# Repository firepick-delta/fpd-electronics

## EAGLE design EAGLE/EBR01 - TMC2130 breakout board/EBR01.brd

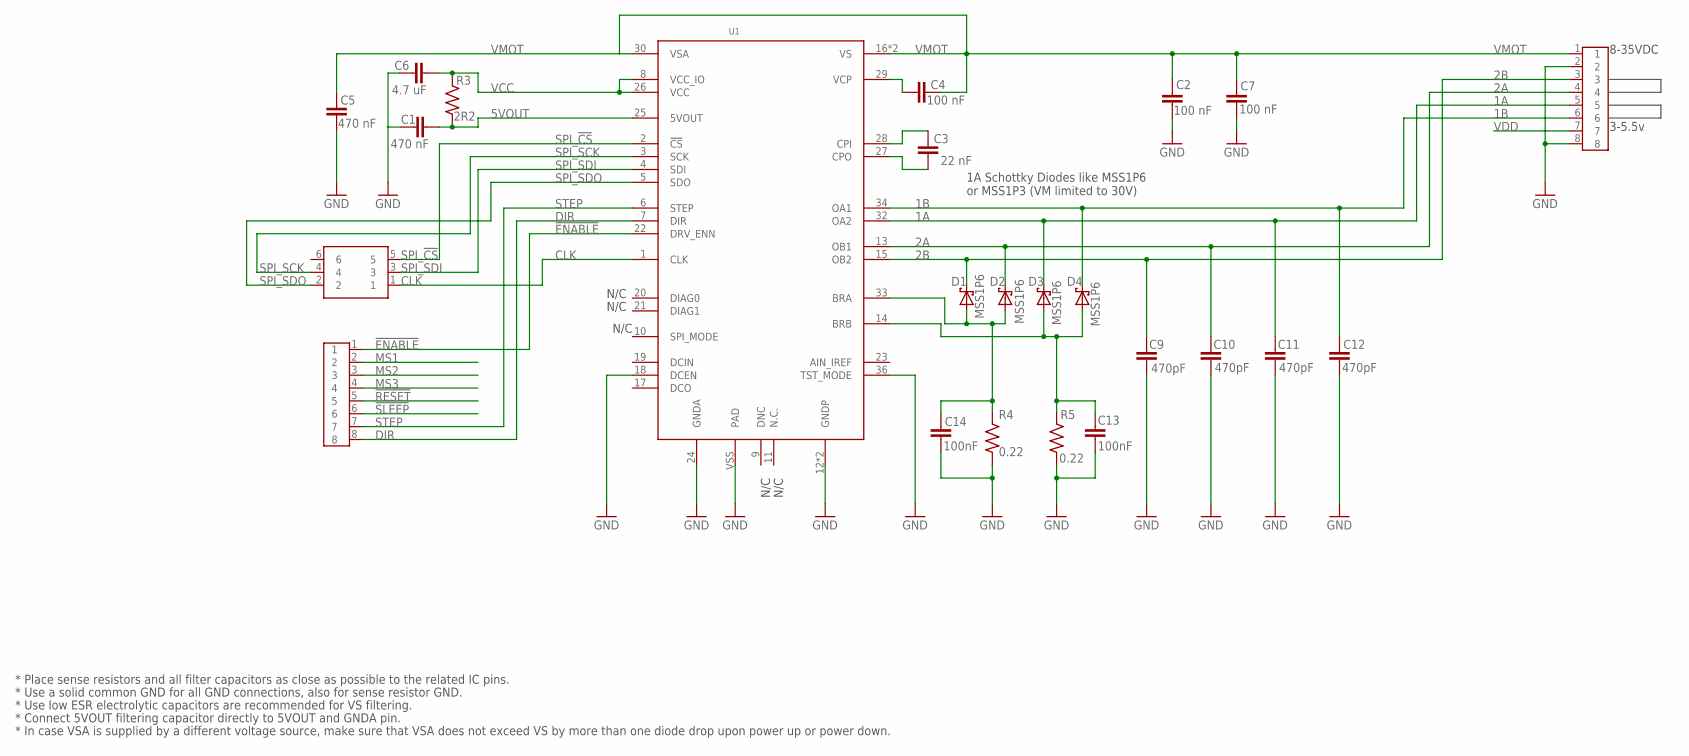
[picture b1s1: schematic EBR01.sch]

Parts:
C1: 470 nF; 0603-CAP
C2, C4, C7: 100 nF; C0603
C3: 22 nF; C0603
C5: 470 nF; C0603
C6: 4.7 uF; C0603
C9, C10, C11, C12: 470pF; C0603
C13, C14: 100nF; C0603
D1, D2, D3, D4: MSS1P6; MICRO-SMP
J1, J2: CPL-CON-HEADER-0.1IN-8P-M; CON-HDR-8POS-MALE
J3: CPL-CON-HEADER-0.1IN-2X3P-M; CON-HDR-2X3P
R3: 2R2; R0603
R4, R5: 0.22; R1206
U1: CPL-MDR-2PHSTEPPER; QFN36-(5X6)

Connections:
1A: C11.1, D3.NEG (C), J2.5, U1.32 (OA2)
1B: C12.1, D4.NEG (C), J2.6, U1.34 (OA1)
2A: C10.1, D2.NEG (C), J2.4, U1.13 (OB1)
2B: C9.1, D1.NEG (C), J2.3, U1.15 (OB2)
5VOUT: C1.1, R3.1, U1.25 (5VOUT)
!ENABLE!: J1.1, U1.22 (DRV_ENN)
!RESET!: J1.5
!SLEEP!: J1.6
CLK: J3.1, U1.1 (CLK)
DIR: J1.8, U1.7 (DIR)
GND: C1.2, C2.2, C5.1, C6.2, C7.2, C9.2, C10.2, C11.2, C12.2, C13.2, C14.2, J2.2, J2.8, R4.1, R5.1, U1.12 (GNDP), U1.18 (DCEN), U1.24 (GNDA), U1.35 (GNDP), U1.36 (TST_MODE), U1.VSS (PAD)
MS1: J1.2
MS2: J1.3
MS3: J1.4
unnamed: C3.2, U1.28 (CPI)
unnamed: C14.1, D1.POS (A), D2.POS (A), R4.2, U1.33 (BRA)
unnamed: C13.1, D3.POS (A), D4.POS (A), R5.2, U1.14 (BRB)
unnamed: C3.1, U1.27 (CPO)
unnamed: C4.1, U1.29 (VCP)
SPI_!CS!: J3.5, U1.2 (!CS)
SPI_SCK: J3.4, U1.3 (SCK)
SPI_SDI: J3.3, U1.4 (SDI)
SPI_SDO: J3.2, U1.5 (SDO)
STEP: J1.7, U1.6 (STEP)
VCC: C6.1, R3.2, U1.8 (VCC_IO), U1.26 (VCC)
VDD: J2.7
VMOT: C2.1, C4.2, C5.2, C7.1, J2.1, U1.16 (VS), U1.30 (VSA), U1.31 (VS)

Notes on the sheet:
3-5.5v
8-35VDC
N/C
* Place sense resistors and all filter capacitors as close as possible to the related IC pins.
* Use a solid common GND for all GND connections, also for sense resistor GND.
* Use low ESR electrolytic capacitors are recommended for VS filtering.
* Connect 5VOUT filtering capacitor directly to 5VOUT and GNDA pin.
* In case VSA is supplied by a different voltage source, make sure that VSA does not exceed VS by more than one diode drop upon power up or power down.
1A Schottky Diodes like MSS1P6 or MSS1P3 (VM limited to 30V)

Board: 2 copper layers, 24 parts (0 on the bottom side), 21 nets, no tracks yet.

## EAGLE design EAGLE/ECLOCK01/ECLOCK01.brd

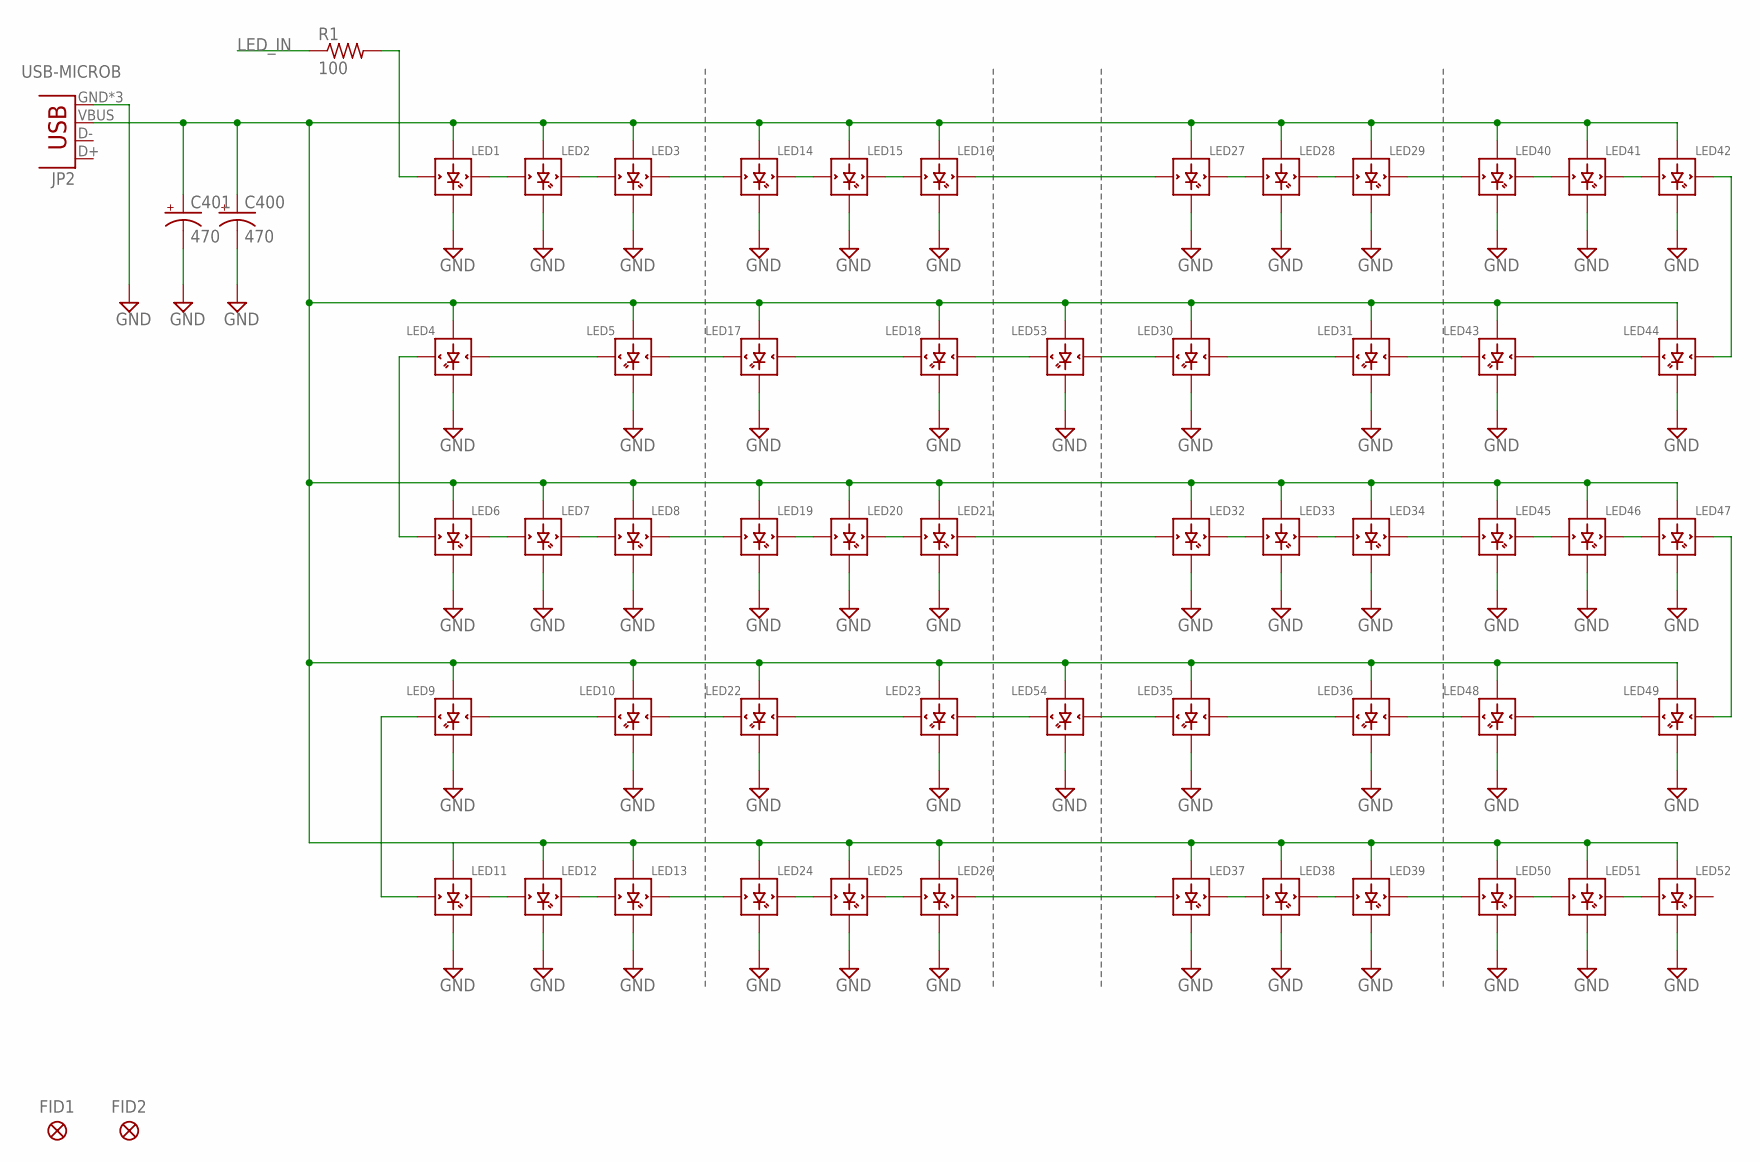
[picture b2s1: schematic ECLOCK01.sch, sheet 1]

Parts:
C400, C401: 470; PANASONIC_E
FID1, FID2: FIDUCIAL
JP2: USB-MICROB
LED1, LED2, LED3, LED4, LED5, LED6, LED7, LED8, LED9, LED10, LED11, LED12, LED13, LED14, LED15, LED16, LED17, LED18, LED19, LED20, LED21, LED22, LED23, LED24, LED25, LED26, LED27, LED28, LED29, LED30, LED31, LED32, LED33, LED34, LED35, LED36, LED37, LED38, LED39, LED40, LED41, LED42, LED43, LED44, LED45, LED46, LED47, LED48, LED49, LED50, LED51, LED52, LED53, LED54: WS2812B
R1: 100; 0805

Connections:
GND: C400.-, C401.-, JP2.GND, JP2.MT1 (GND), JP2.MT2 (GND), LED1.3-GND (GND), LED2.3-GND (GND), LED3.3-GND (GND), LED4.3-GND (GND), LED5.3-GND (GND), LED6.3-GND (GND), LED7.3-GND (GND), LED8.3-GND (GND), LED9.3-GND (GND), LED10.3-GND (GND), LED11.3-GND (GND), LED12.3-GND (GND), LED13.3-GND (GND), LED14.3-GND (GND), LED15.3-GND (GND), LED16.3-GND (GND), LED17.3-GND (GND), LED18.3-GND (GND), LED19.3-GND (GND), LED20.3-GND (GND), LED21.3-GND (GND), LED22.3-GND (GND), LED23.3-GND (GND), LED24.3-GND (GND), LED25.3-GND (GND), LED26.3-GND (GND), LED27.3-GND (GND), LED28.3-GND (GND), LED29.3-GND (GND), LED30.3-GND (GND), LED31.3-GND (GND), LED32.3-GND (GND), LED33.3-GND (GND), LED34.3-GND (GND), LED35.3-GND (GND), LED36.3-GND (GND), LED37.3-GND (GND), LED38.3-GND (GND), LED39.3-GND (GND), LED40.3-GND (GND), LED41.3-GND (GND), LED42.3-GND (GND), LED43.3-GND (GND), LED44.3-GND (GND), LED45.3-GND (GND), LED46.3-GND (GND), LED47.3-GND (GND), LED48.3-GND (GND), LED49.3-GND (GND), LED50.3-GND (GND), LED51.3-GND (GND), LED52.3-GND (GND), LED53.3-GND (GND), LED54.3-GND (GND); also elsewhere on the board
LED_IN: R1.1; also elsewhere on the board
unnamed: LED1.4-DIN (DIN), R1.2
unnamed: LED11.2-DOUT (DOUT), LED12.4-DIN (DIN)
unnamed: LED1.2-DOUT (DOUT), LED2.4-DIN (DIN)
unnamed: LED2.2-DOUT (DOUT), LED3.4-DIN (DIN)
unnamed: LED16.2-DOUT (DOUT), LED27.4-DIN (DIN)
unnamed: LED12.2-DOUT (DOUT), LED13.4-DIN (DIN)
unnamed: LED26.2-DOUT (DOUT), LED37.4-DIN (DIN)
unnamed: LED14.2-DOUT (DOUT), LED15.4-DIN (DIN)
unnamed: LED15.2-DOUT (DOUT), LED16.4-DIN (DIN)
unnamed: LED18.4-DIN (DIN), LED53.2-DOUT (DOUT)
unnamed: LED19.2-DOUT (DOUT), LED20.4-DIN (DIN)
unnamed: LED17.4-DIN (DIN), LED18.2-DOUT (DOUT)
unnamed: LED8.2-DOUT (DOUT), LED19.4-DIN (DIN)
unnamed: LED47.2-DOUT (DOUT), LED49.4-DIN (DIN)
unnamed: LED39.2-DOUT (DOUT), LED50.4-DIN (DIN)
unnamed: LED24.2-DOUT (DOUT), LED25.4-DIN (DIN)
unnamed: LED25.2-DOUT (DOUT), LED26.4-DIN (DIN)
unnamed: LED13.2-DOUT (DOUT), LED24.4-DIN (DIN)
unnamed: LED27.2-DOUT (DOUT), LED28.4-DIN (DIN)
unnamed: LED28.2-DOUT (DOUT), LED29.4-DIN (DIN)
unnamed: LED40.2-DOUT (DOUT), LED41.4-DIN (DIN)
unnamed: LED20.2-DOUT (DOUT), LED21.4-DIN (DIN)
unnamed: LED9.2-DOUT (DOUT), LED11.4-DIN (DIN)
unnamed: LED5.4-DIN (DIN), LED17.2-DOUT (DOUT)
unnamed: LED4.4-DIN (DIN), LED5.2-DOUT (DOUT)
unnamed: LED6.2-DOUT (DOUT), LED7.4-DIN (DIN)
unnamed: LED7.2-DOUT (DOUT), LED8.4-DIN (DIN)
unnamed: LED21.2-DOUT (DOUT), LED32.4-DIN (DIN)
unnamed: LED48.4-DIN (DIN), LED49.2-DOUT (DOUT)
unnamed: LED36.4-DIN (DIN), LED48.2-DOUT (DOUT)
unnamed: LED37.2-DOUT (DOUT), LED38.4-DIN (DIN)
unnamed: LED38.2-DOUT (DOUT), LED39.4-DIN (DIN)
unnamed: LED30.2-DOUT (DOUT), LED53.4-DIN (DIN)
unnamed: LED34.2-DOUT (DOUT), LED45.4-DIN (DIN)
unnamed: LED32.2-DOUT (DOUT), LED33.4-DIN (DIN)
unnamed: LED33.2-DOUT (DOUT), LED34.4-DIN (DIN)
unnamed: LED31.4-DIN (DIN), LED43.2-DOUT (DOUT)
unnamed: LED4.2-DOUT (DOUT), LED6.4-DIN (DIN)
unnamed: LED46.2-DOUT (DOUT), LED47.4-DIN (DIN)
unnamed: LED45.2-DOUT (DOUT), LED46.4-DIN (DIN)
unnamed: LED42.2-DOUT (DOUT), LED44.4-DIN (DIN)
unnamed: LED43.4-DIN (DIN), LED44.2-DOUT (DOUT)
unnamed: LED30.4-DIN (DIN), LED31.2-DOUT (DOUT)
unnamed: LED41.2-DOUT (DOUT), LED42.4-DIN (DIN)
unnamed: LED35.4-DIN (DIN), LED36.2-DOUT (DOUT)
unnamed: LED35.2-DOUT (DOUT), LED54.4-DIN (DIN)
unnamed: LED50.2-DOUT (DOUT), LED51.4-DIN (DIN)
unnamed: LED51.2-DOUT (DOUT), LED52.4-DIN (DIN)
unnamed: LED23.4-DIN (DIN), LED54.2-DOUT (DOUT)
unnamed: LED22.4-DIN (DIN), LED23.2-DOUT (DOUT)
unnamed: LED3.2-DOUT (DOUT), LED14.4-DIN (DIN)
unnamed: LED10.4-DIN (DIN), LED22.2-DOUT (DOUT)
unnamed: LED9.4-DIN (DIN), LED10.2-DOUT (DOUT)
unnamed: LED29.2-DOUT (DOUT), LED40.4-DIN (DIN)
VDD: C400.+, C401.+, JP2.VBUS, LED1.1-VDD (VDD), LED2.1-VDD (VDD), LED3.1-VDD (VDD), LED4.1-VDD (VDD), LED5.1-VDD (VDD), LED6.1-VDD (VDD), LED7.1-VDD (VDD), LED8.1-VDD (VDD), LED9.1-VDD (VDD), LED10.1-VDD (VDD), LED11.1-VDD (VDD), LED12.1-VDD (VDD), LED13.1-VDD (VDD), LED14.1-VDD (VDD), LED15.1-VDD (VDD), LED16.1-VDD (VDD), LED17.1-VDD (VDD), LED18.1-VDD (VDD), LED19.1-VDD (VDD), LED20.1-VDD (VDD), LED21.1-VDD (VDD), LED22.1-VDD (VDD), LED23.1-VDD (VDD), LED24.1-VDD (VDD), LED25.1-VDD (VDD), LED26.1-VDD (VDD), LED27.1-VDD (VDD), LED28.1-VDD (VDD), LED29.1-VDD (VDD), LED30.1-VDD (VDD), LED31.1-VDD (VDD), LED32.1-VDD (VDD), LED33.1-VDD (VDD), LED34.1-VDD (VDD), LED35.1-VDD (VDD), LED36.1-VDD (VDD), LED37.1-VDD (VDD), LED38.1-VDD (VDD), LED39.1-VDD (VDD), LED40.1-VDD (VDD), LED41.1-VDD (VDD), LED42.1-VDD (VDD), LED43.1-VDD (VDD), LED44.1-VDD (VDD), LED45.1-VDD (VDD), LED46.1-VDD (VDD), LED47.1-VDD (VDD), LED48.1-VDD (VDD), LED49.1-VDD (VDD), LED50.1-VDD (VDD), LED51.1-VDD (VDD), LED52.1-VDD (VDD), LED53.1-VDD (VDD), LED54.1-VDD (VDD); also elsewhere on the board

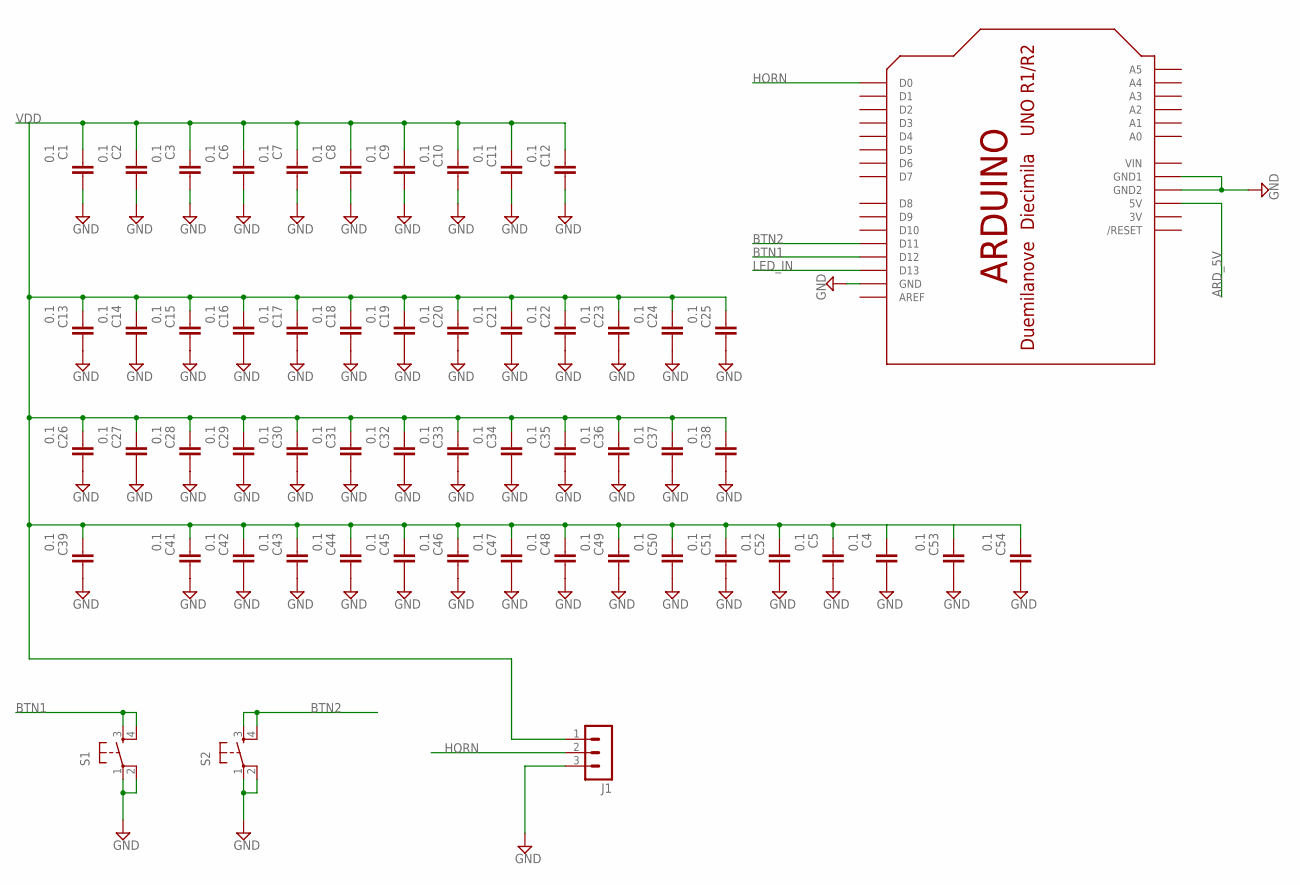
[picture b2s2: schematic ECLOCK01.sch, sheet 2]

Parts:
C1, C2, C3, C4, C5, C6, C7, C8, C9, C10, C11, C12, C13, C14, C15, C16, C17, C18, C19, C20, C21, C22, C23, C24, C25, C26, C27, C28, C29, C30, C31, C32, C33, C34, C35, C36, C37, C38, C39, C41, C42, C43, C44, C45, C46, C47, C48, C49, C50, C51, C52, C53, C54: 0.1; 0805
J1: MA03-1
S1, S2: TAC_SWITCHSMD; TACTILE_SWITCH_SMD
U$1: ARDUINOUNO; ARDUINO-UNO

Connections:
3V: U$1.3V
ARD_5V: U$1.5V
BTN1: S1.3, S1.4, U$1.D12
BTN2: S2.3, S2.4, U$1.D11
GND: C1.2, C2.2, C3.2, C4.2, C5.2, C6.2, C7.2, C8.2, C9.2, C10.2, C11.2, C12.2, C13.2, C14.2, C15.2, C16.2, C17.2, C18.2, C19.2, C20.2, C21.2, C22.2, C23.2, C24.2, C25.2, C26.2, C27.2, C28.2, C29.2, C30.2, C31.2, C32.2, C33.2, C34.2, C35.2, C36.2, C37.2, C38.2, C39.2, C41.2, C42.2, C43.2, C44.2, C45.2, C46.2, C47.2, C48.2, C49.2, C50.2, C51.2, C52.2, C53.2, C54.2, J1.3, S1.1, S1.2, S2.1, S2.2, U$1.GND, U$1.GND1, U$1.GND2; also elsewhere on the board
HORN: J1.2, U$1.D0
LED_IN: U$1.D13; also elsewhere on the board
VDD: C1.1, C2.1, C3.1, C4.1, C5.1, C6.1, C7.1, C8.1, C9.1, C10.1, C11.1, C12.1, C13.1, C14.1, C15.1, C16.1, C17.1, C18.1, C19.1, C20.1, C21.1, C22.1, C23.1, C24.1, C25.1, C26.1, C27.1, C28.1, C29.1, C30.1, C31.1, C32.1, C33.1, C34.1, C35.1, C36.1, C37.1, C38.1, C39.1, C41.1, C42.1, C43.1, C44.1, C45.1, C46.1, C47.1, C48.1, C49.1, C50.1, C51.1, C52.1, C53.1, C54.1, J1.1; also elsewhere on the board
VIN: U$1.VIN

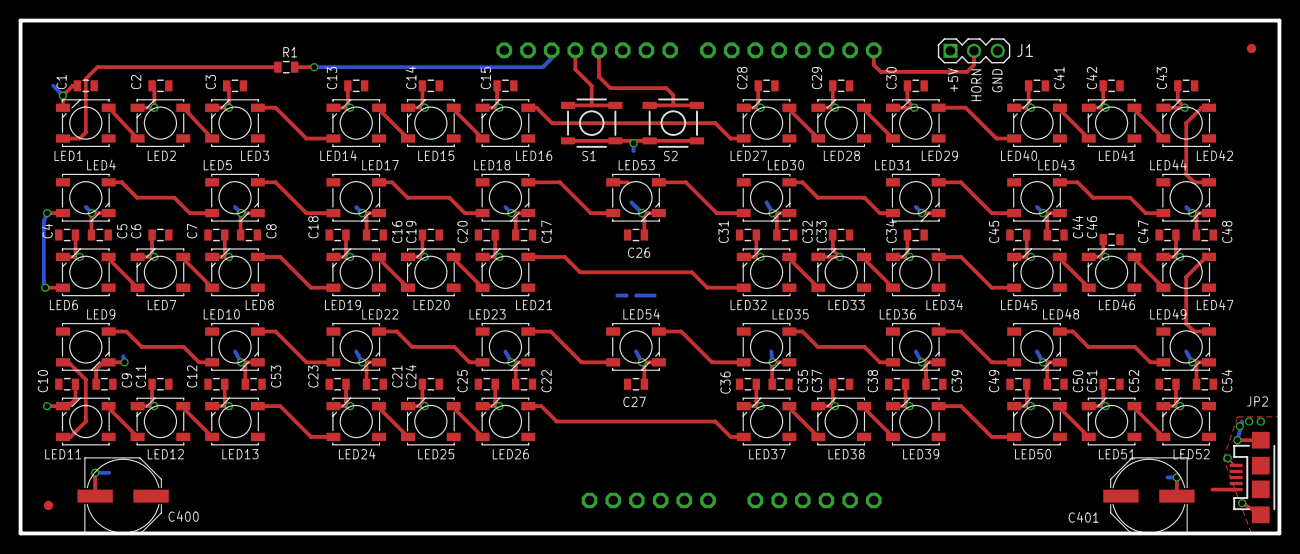
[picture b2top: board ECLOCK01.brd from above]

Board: 2 copper layers, 135.0 x 55.0 mm, 117 parts (0 on the bottom side), 60 nets.

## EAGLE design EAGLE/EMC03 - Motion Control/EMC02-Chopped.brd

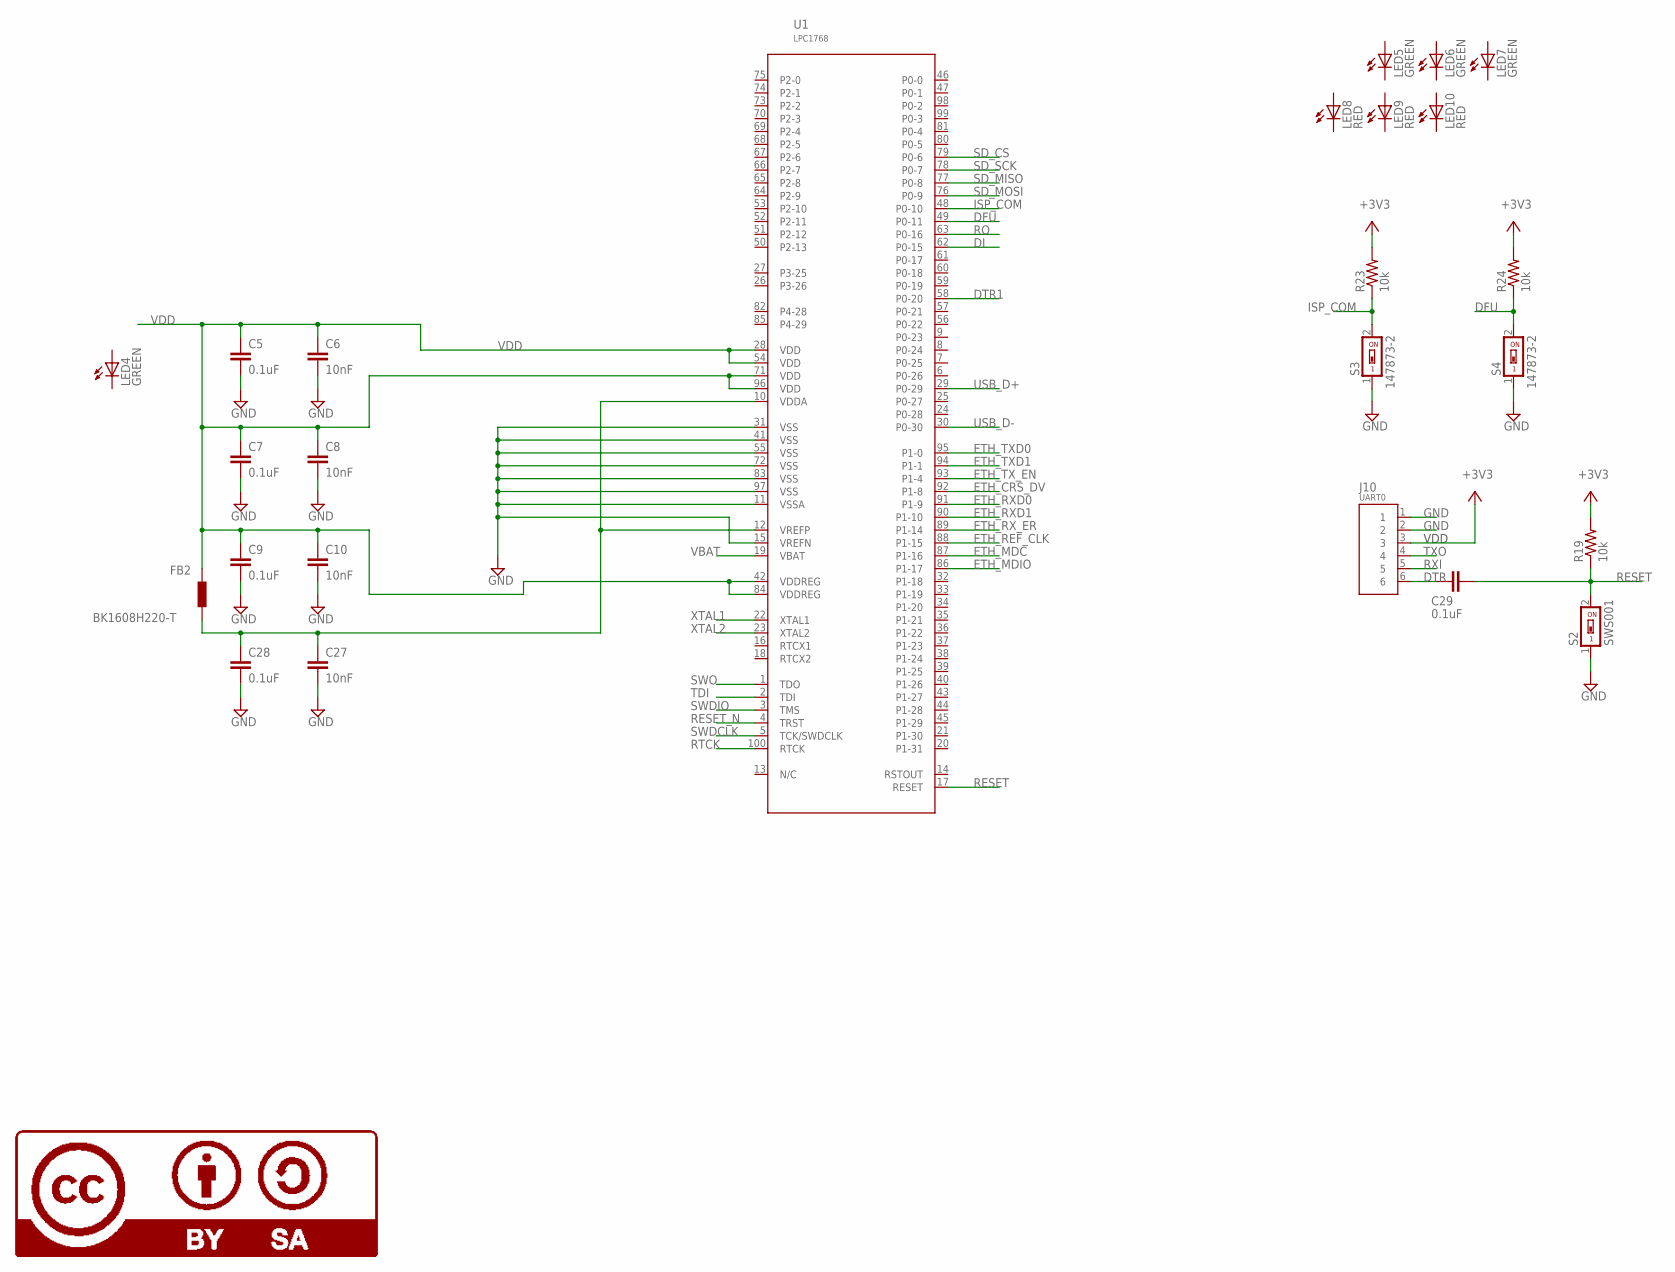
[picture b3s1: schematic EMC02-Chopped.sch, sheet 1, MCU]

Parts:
C5, C7, C9, C28, C29: 0.1uF; C0603
C6, C8, C10, C27: 10nF; C0603
FB2: BK1608H220-T; F0603
J10: UART0; CON-HDR-6POS-MALE
LED4, LED5, LED6, LED7: GREEN; LED0603
LED8, LED9, LED10: RED; LED0603
LOGO8: LOGO-CC-BY-SALARGE; LOGO-CC-BY-SA
R19, R23, R24: 10k; R0603
S2: SWS001; SMS-001
S3, S4: 147873-2; 0603
U1: LPC1768; LQFP-100

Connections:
+3V3: J10.3, R19.2, R23.2, R24.2; also elsewhere on the board
DFU: R24.1, S4.2, U1.49 (P0-11)
DI: U1.62 (P0-15); also elsewhere on the board
DTR: C29.1, J10.6
DTR1: U1.58 (P0-20); also elsewhere on the board
ETH_CRS_DV: U1.92 (P1-8); also elsewhere on the board
ETH_MDC: U1.87 (P1-16); also elsewhere on the board
ETH_MDIO: U1.86 (P1-17); also elsewhere on the board
ETH_REF_CLK: U1.88 (P1-15); also elsewhere on the board
ETH_RXD0: U1.91 (P1-9); also elsewhere on the board
ETH_RXD1: U1.90 (P1-10); also elsewhere on the board
ETH_RX_ER: U1.89 (P1-14); also elsewhere on the board
ETH_TXD0: U1.95 (P1-0); also elsewhere on the board
ETH_TXD1: U1.94 (P1-1); also elsewhere on the board
ETH_TX_EN: U1.93 (P1-4); also elsewhere on the board
GND: C5.1, C6.1, C7.1, C8.1, C9.1, C10.1, C28.1, J10.1, J10.2, S2.1, S3.1, S4.1, U1.11 (VSSA), U1.15 (VREFN), U1.31 (VSS), U1.41 (VSS), U1.55 (VSS), U1.72 (VSS), U1.83 (VSS), U1.97 (VSS); also elsewhere on the board
GND1: C27.1
ISP_COM: R23.1, S3.2, U1.48 (P0-10)
unnamed: C27.2, C28.2, FB2.1, U1.10 (VDDA), U1.12 (VREFP)
RESET: C29.2, R19.1, S2.2, U1.17 (RESET)
RESET_N: U1.4 (TRST); also elsewhere on the board
RO: U1.63 (P0-16); also elsewhere on the board
RTCK: U1.100 (RTCK); also elsewhere on the board
RXI: J10.5
SD_CS: U1.79 (P0-6); also elsewhere on the board
SD_MISO: U1.77 (P0-8); also elsewhere on the board
SD_MOSI: U1.76 (P0-9); also elsewhere on the board
SD_SCK: U1.78 (P0-7); also elsewhere on the board
SWDCLK: U1.5 (TCK/SWDCLK); also elsewhere on the board
SWDIO: U1.3 (TMS); also elsewhere on the board
SWO: U1.1 (TDO); also elsewhere on the board
TDI: U1.2 (TDI); also elsewhere on the board
TXO: J10.4
USB_D+: U1.29 (P0-29); also elsewhere on the board
USB_D-: U1.30 (P0-30); also elsewhere on the board
VBAT: U1.19 (VBAT)
VDD: C5.2, C6.2, C7.2, C8.2, C9.2, C10.2, FB2.2, U1.28 (VDD), U1.42 (VDDREG), U1.54 (VDD), U1.71 (VDD), U1.84 (VDDREG), U1.96 (VDD)
XTAL1: U1.22 (XTAL1); also elsewhere on the board
XTAL2: U1.23 (XTAL2); also elsewhere on the board

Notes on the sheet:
VDD

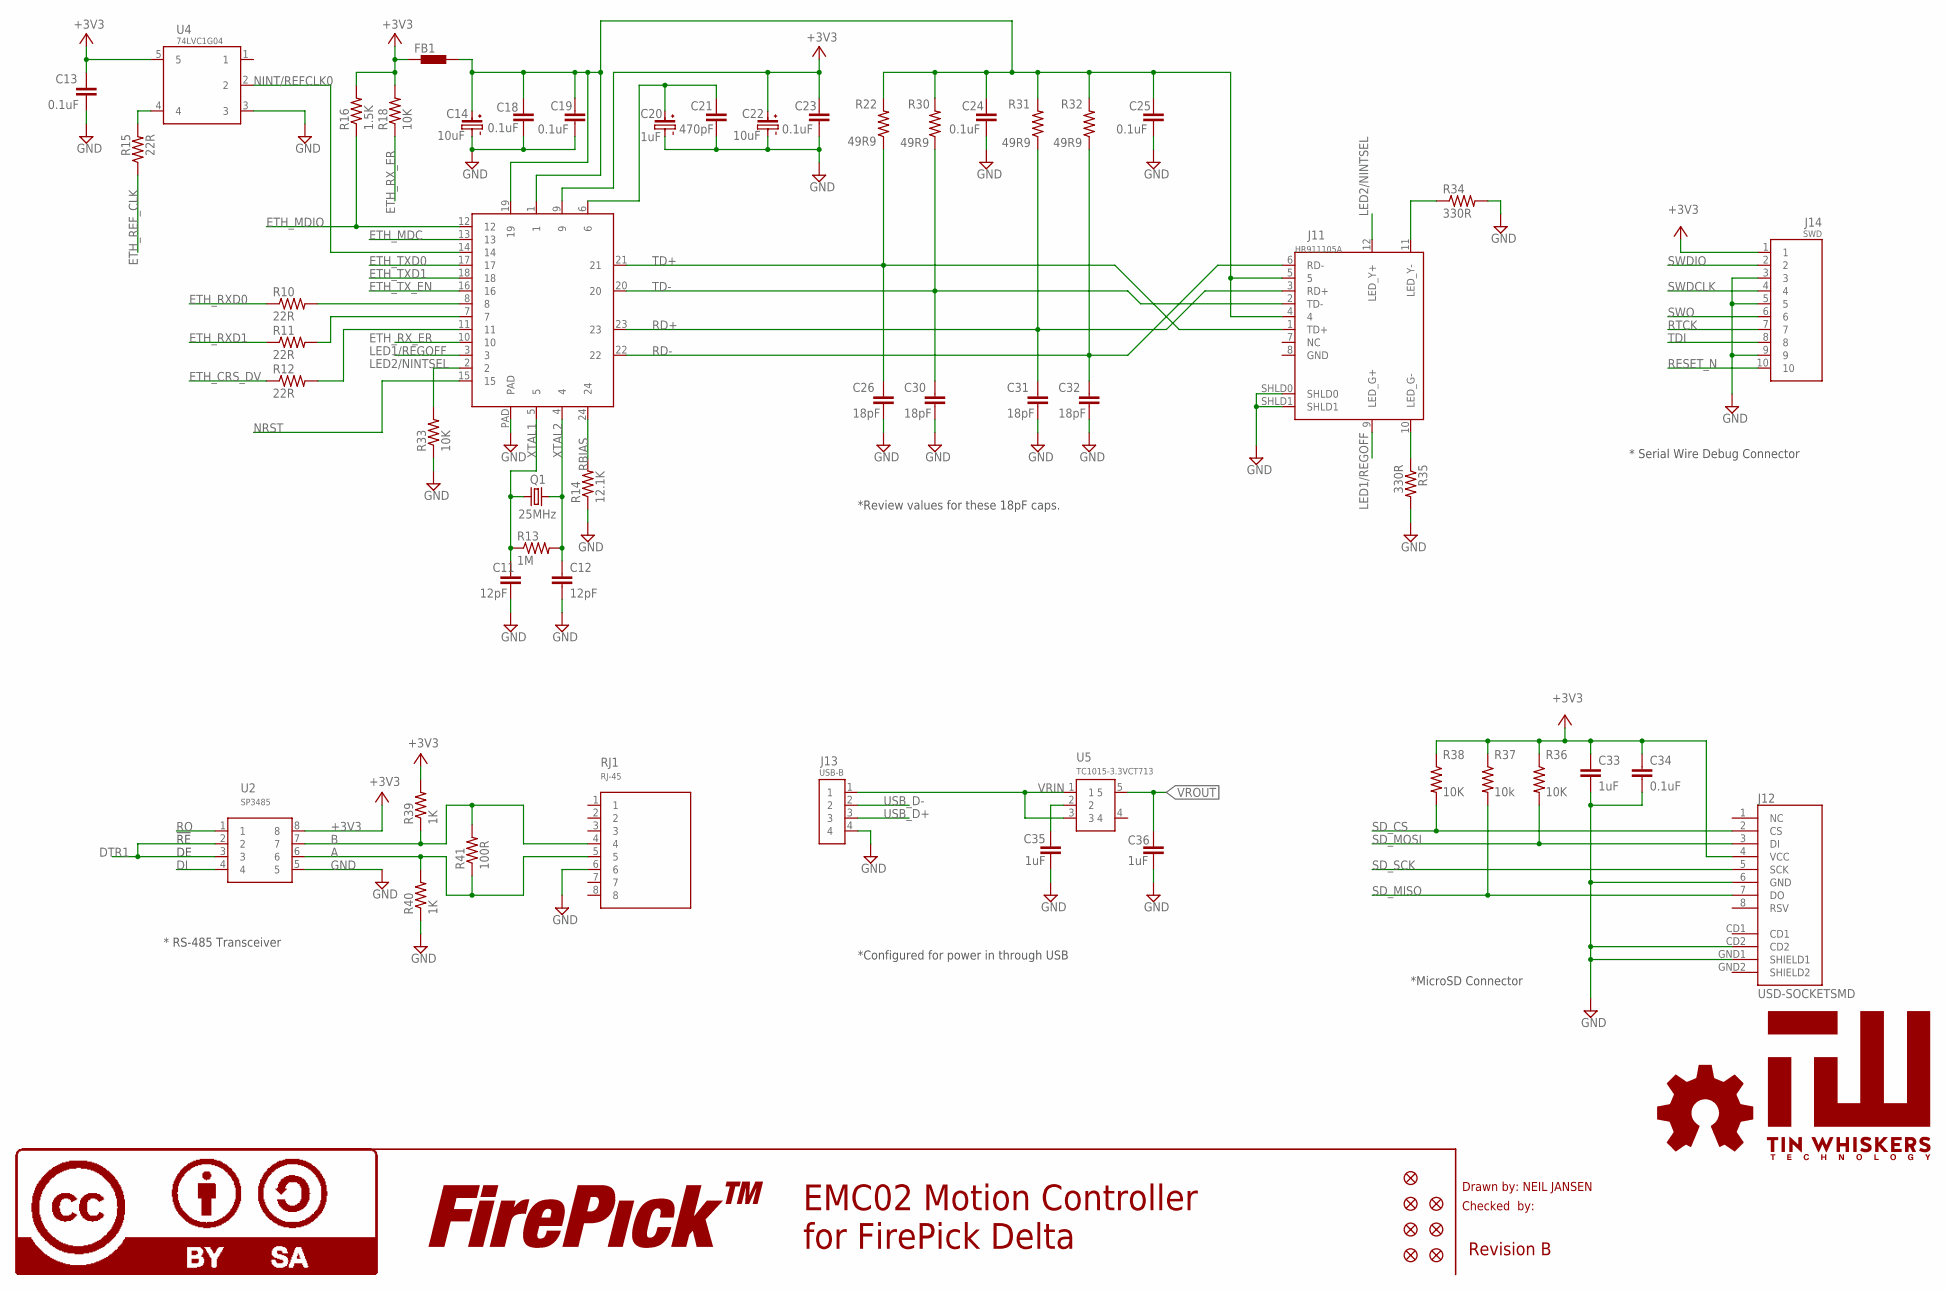
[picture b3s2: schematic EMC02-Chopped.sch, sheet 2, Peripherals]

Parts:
C11, C12: 12pF; C0603
C13, C18, C19, C23, C24, C25, C34: 0.1uF; C0603
C14, C22: 10uF; C-RAD-6.3MM
C20: 1uF; C-SMD-4MM
C21: 470pF; C0603
C26, C30, C31, C32: 18pF; C0603
C33, C35, C36: 1uF; C0603
FB1: BLM15HBK1608H220-T0603; F0603
FID1, FID2, FID3, FID4, FID5, FID6, FID7: FIDUCIAL
J11: HR911105A; MAGJACK(HR911105A)
J12: USD-SOCKETSMD; MICRO-SD-SOCKET-PP
J13: USB-B; USB-B(THRU)
J14: SWD; FTSH-105-01-XXX-DV-K
LOGO4: LOGO-FIREPICKLARGE; LOGO-FIREPICK
LOGO5: LOGO-OSHWMEDIUM; LOGO-OSHW-MEDIUM
LOGO6: LOGO-CC-BY-SALARGE; LOGO-CC-BY-SA
Q1: 25MHz; HC-49/U-S
R10, R11, R12, R15: 22R; R0603
R13: 1M; R0603
R14: 12.1K; R0603
R16: 1.5K; R0603
R18, R33, R36, R38: 10K; R0603
R22, R30, R31, R32: 49R9; R0603
R34, R35: 330R; R0603
R37: 10k; R0603
R39, R40: 1K; R0603
R41: 100R; R0603
RJ1: RJ-45; CON-RJ45
U2: SP3485; SOICN-8
U3: CPL-ETH-PHY-LAN8720A; QFN-24
U4: 74LVC1G04; SOT-25
U5: TC1015-3.3VCT713; SOT-23-5
U$25: TIN-WHISKERSTSTOP; TIN-WHISKERS-TSTOP

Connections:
+3V3: C13.2, C22.POS, C23.2, C33.2, C34.2, FB1.1, J12.4 (VCC), J14.1, R16.2, R18.2, R36.1, R37.1, R38.1, R39.2, U2.8, U3.9, U4.5; also elsewhere on the board
A: R40.2, R41.1, RJ1.5, U2.6
B: R39.1, R41.2, RJ1.4, U2.7
DI: U2.4; also elsewhere on the board
DTR1: U2.2, U2.3; also elsewhere on the board
ETH_CRS_DV: R12.1; also elsewhere on the board
ETH_MDC: U3.13; also elsewhere on the board
ETH_MDIO: R16.1, U3.12; also elsewhere on the board
ETH_REF_CLK: R15.1; also elsewhere on the board
ETH_RXD0: R10.1; also elsewhere on the board
ETH_RXD1: R11.1; also elsewhere on the board
ETH_RX_ER: R18.1, U3.10; also elsewhere on the board
ETH_TXD0: U3.17; also elsewhere on the board
ETH_TXD1: U3.18; also elsewhere on the board
ETH_TX_EN: U3.16; also elsewhere on the board
GND: C11.1, C12.1, C13.1, C14.NEG, C18.1, C19.1, C20.NEG, C21.1, C22.NEG, C23.1, C24.1, C25.1, C26.1, C30.1, C31.1, C32.1, C33.1, C34.1, C35.1, C36.1, J11.SHLD0, J11.SHLD1, J12.6 (GND), J12.CD2, J12.GND1 (SHIELD1), J13.4, J14.3, J14.5, J14.9, R14.1, R33.1, R34.2, R35.2, R40.1, RJ1.6, U2.5, U3.PAD, U4.3; also elsewhere on the board
LED1/REGOFF: J11.9 (LED_G+), U3.3
LED2/NINTSEL: J11.12 (LED_Y+), R33.2, U3.2
unnamed: R10.2, U3.8
unnamed: R15.2, U4.4
unnamed: C14.POS, C18.2, C19.2, C24.2, C25.2, FB1.2, J11.4, J11.5, R22.2, R30.2, R31.2, R32.2, U3.1, U3.19
unnamed: J11.11 (LED_Y-), R34.1
unnamed: J11.10 (LED_G-), R35.1
unnamed: C35.2, U5.2
unnamed: R11.2, U3.7
unnamed: R12.2, U3.11
unnamed: C20.POS, C21.2, U3.6
NINT/REFCLK0: U3.14, U4.2
NRST: U3.15
RBIAS: R14.2, U3.24
RD+: C31.2, J11.3 (RD+), R31.1, U3.23
RD-: C32.2, J11.6 (RD-), R32.1, U3.22
RESET_N: J14.10; also elsewhere on the board
RO: U2.1; also elsewhere on the board
RTCK: J14.7; also elsewhere on the board
SD_CS: J12.2 (CS), R38.2; also elsewhere on the board
SD_MISO: J12.7 (DO), R37.2; also elsewhere on the board
SD_MOSI: J12.3 (DI), R36.2; also elsewhere on the board
SD_SCK: J12.5 (SCK); also elsewhere on the board
SWDCLK: J14.4; also elsewhere on the board
SWDIO: J14.2; also elsewhere on the board
SWO: J14.6; also elsewhere on the board
TD+: C26.2, J11.1 (TD+), R22.1, U3.21
TD-: C30.2, J11.2 (TD-), R30.1, U3.20
TDI: J14.8; also elsewhere on the board
USB_D+: J13.3; also elsewhere on the board
USB_D-: J13.2; also elsewhere on the board
VRIN: J13.1, U5.1, U5.3
VROUT: C36.2, U5.5
XTAL1: C11.2, Q1.1, R13.1, U3.5; also elsewhere on the board
XTAL2: C12.2, Q1.2, R13.2, U3.4; also elsewhere on the board

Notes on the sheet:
Drawn by: NEIL JANSEN
Checked by:
Revision B
EMC02 Motion Controller for FirePick Delta
*Configured for power in through USB
*Review values for these 18pF caps.
*MicroSD Connector
!RE
* Serial Wire Debug Connector
* RS-485 Transceiver

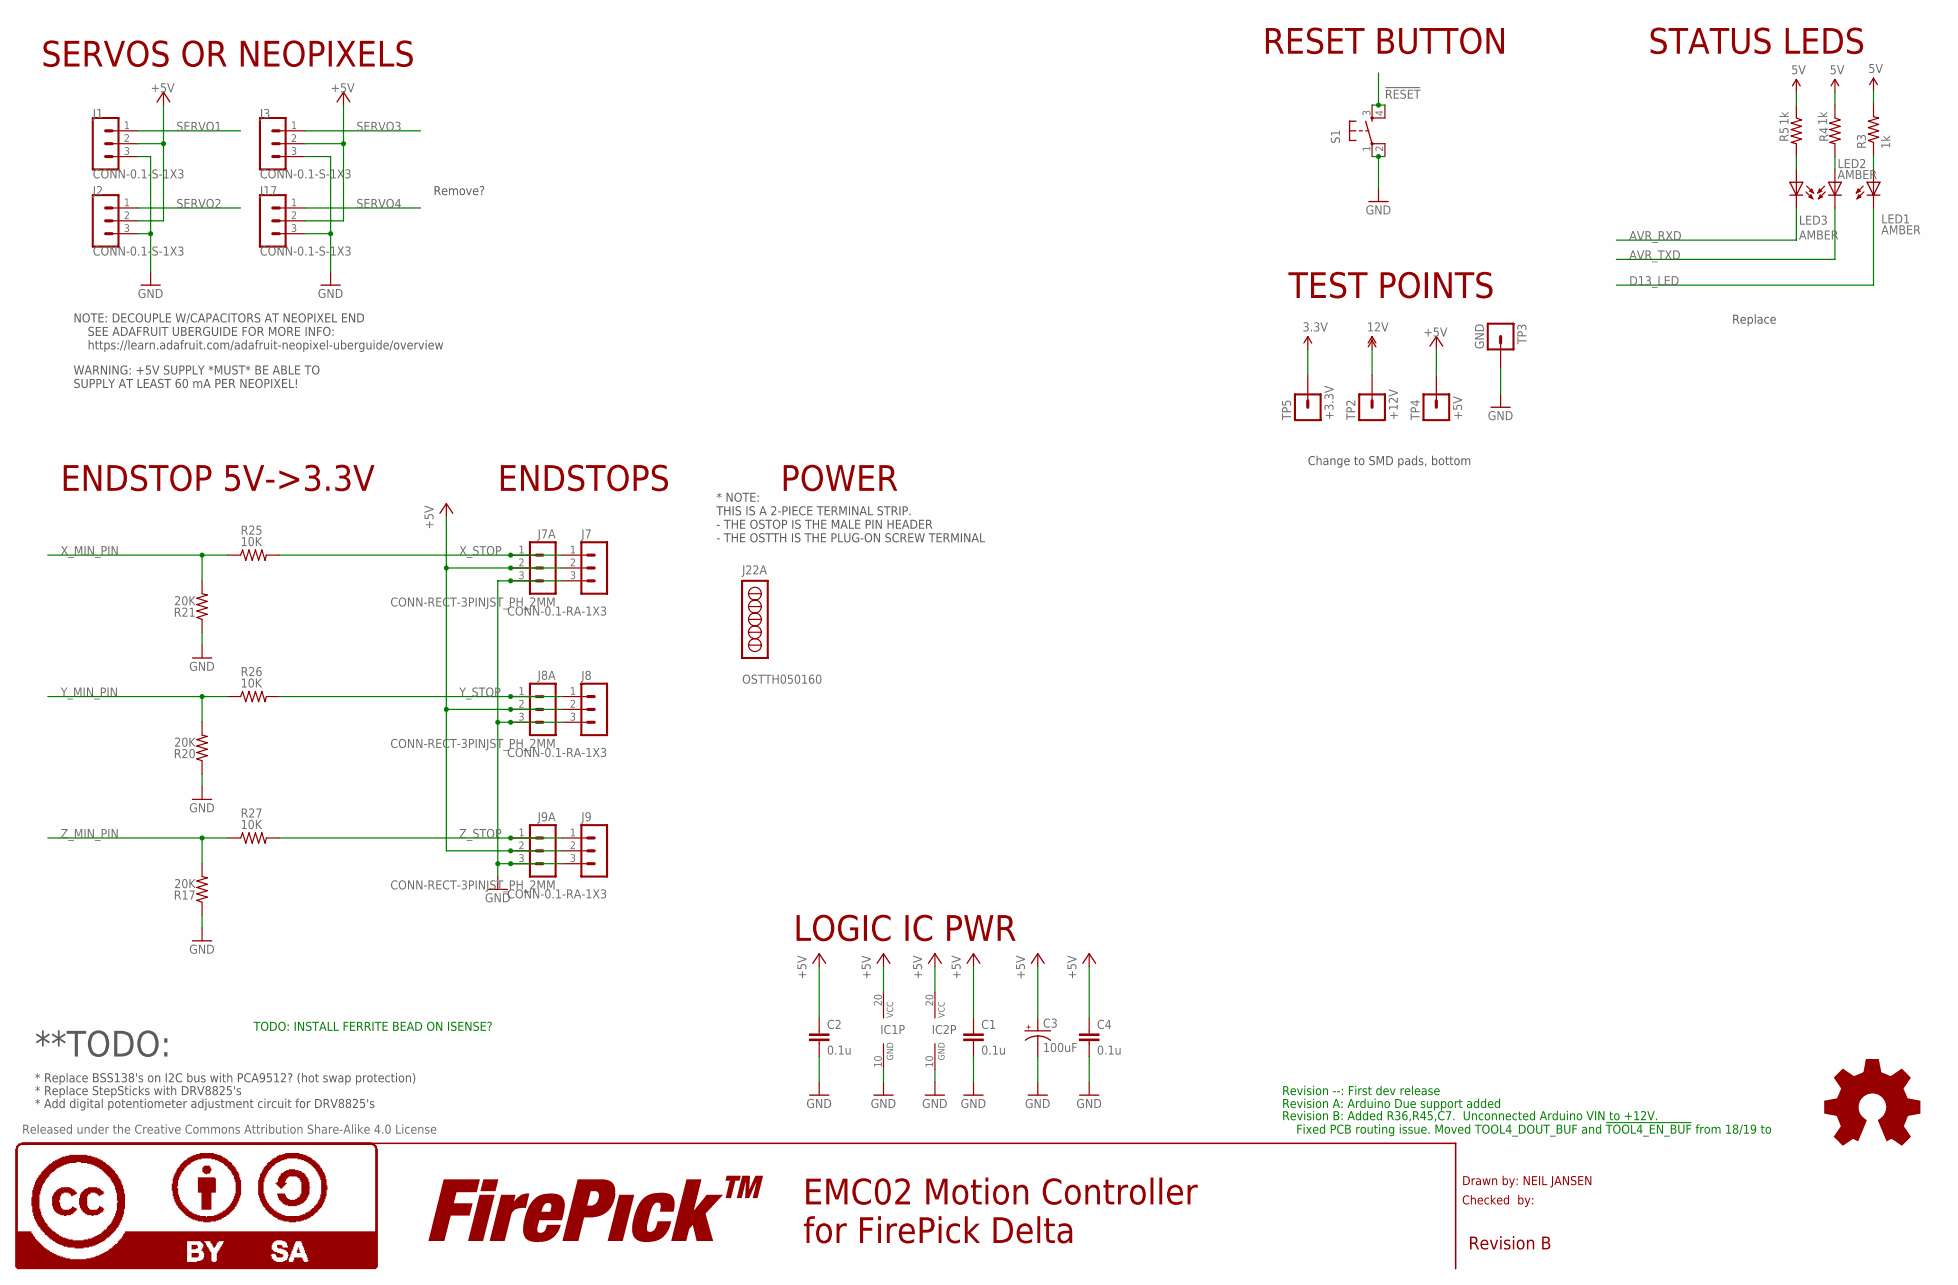
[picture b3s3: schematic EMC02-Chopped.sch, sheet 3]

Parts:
C1, C2, C4: 0.1u; 0805; PARTNO CC0805ZRY5V9BB104
C3: 100uF; PANASONIC_D; PARTNO 25TXV100M6.3X8
IC1, IC2: 74ACT244DW; SO20W; PARTNO 74ACT244SCX
J1, J2, J3, J17: CONN-0.1-S-1X3; MA03-1; PARTNO CONN-0.1-S-1X3
J7, J8, J9: CONN-0.1-RA-1X3; MA03-1; PARTNO CONN-0.1-RA-1X3
J7A, J8A, J9A: CONN-RECT-3PINJST_PH_2MM; CONN-JST_PH-2.0MM-3PIN-SMT-RA
J22A: OSTTH050160; CONN-OSTTH050160; PARTNO OSTTH050160
LED1, LED2, LED3: AMBER; LED-1206-NO_SILK; PARTNO LTST-C150AKT
LOGO1: LOGO-FIREPICKLARGE; LOGO-FIREPICK
LOGO2: LOGO-OSHWMEDIUM; LOGO-OSHW-MEDIUM
LOGO3: LOGO-CC-BY-SALARGE; LOGO-CC-BY-SA
R3, R4, R5: 1k; 0805; PARTNO RC0805FR-071KL
R17, R20, R21: 20K; 0805; PARTNO RC0805FR-0720KL
R25, R26, R27: 10K; 0805; PARTNO RC0805FR-0710KL
S1: TAC_SWITCHSMD; TACTILE_SWITCH_SMD; PARTNO SWITCH TACTILE SPST-NO 0.05A 12V
TP2: +12V; CON-TESTPOINT
TP3: GND; CON-TESTPOINT
TP4: +5V; CON-TESTPOINT
TP5: +3.3V; CON-TESTPOINT

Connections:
3.3V: TP5.1
12V: TP2.1; also elsewhere on the board
!RESET: S1.3, S1.4
+5V: C1.1, C2.1, C3.+, C4.1, IC1.20 (VCC), IC2.20 (VCC), J1.2, J2.2, J3.2, J7.2, J7A.2, J8.2, J8A.2, J9.2, J9A.2, J17.2, R3.2, R4.1, R5.1, TP4.1; also elsewhere on the board
AVR_RXD: LED3.C
AVR_TXD: LED2.C
D13_LED: LED1.C
GND: C1.2, C2.2, C3.-, C4.2, IC1.10 (GND), IC2.10 (GND), J1.3, J2.3, J3.3, J7.3, J7A.3, J8.3, J8A.3, J9.3, J9A.3, J17.3, R17.1, R20.1, R21.1, S1.1, S1.2, TP3.1; also elsewhere on the board
unnamed: LED1.A, R3.1
unnamed: LED2.A, R4.2
unnamed: LED3.A, R5.2
SERVO1: J1.1; also elsewhere on the board
SERVO2: J2.1; also elsewhere on the board
SERVO3: J3.1; also elsewhere on the board
SERVO4: J17.1; also elsewhere on the board
X_MIN_PIN: R21.2, R25.1
X_STOP: J7.1, J7A.1, R25.2
Y_MIN_PIN: R20.2, R26.1
Y_STOP: J8.1, J8A.1, R26.2
Z_MIN_PIN: R17.2, R27.1
Z_STOP: J9.1, J9A.1, R27.2

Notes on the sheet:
Drawn by: NEIL JANSEN
Checked by:
Revision B
EMC02 Motion Controller for FirePick Delta
Released under the Creative Commons Attribution Share-Alike 4.0 License
**TODO:
* Replace StepSticks with DRV8825's
* Add digital potentiometer adjustment circuit for DRV8825's
* Replace BSS138's on I2C bus with PCA9512? (hot swap protection)
TEST POINTS
WARNING: +5V SUPPLY *MUST* BE ABLE TO SUPPLY AT LEAST 60 mA PER NEOPIXEL!
SERVOS OR NEOPIXELS
RESET BUTTON
STATUS LEDS
ENDSTOP 5V->3.3V
ENDSTOPS
LOGIC IC PWR
POWER
Revision --: First dev release
Revision A: Arduino Due support added
NOTE: DECOUPLE W/CAPACITORS AT NEOPIXEL END SEE ADAFRUIT UBERGUIDE FOR MORE INFO: https://learn.adafruit.com/adafruit-neopixel-uberguide/overview
* NOTE: THIS IS A 2-PIECE TERMINAL STRIP. - THE OSTOP IS THE MALE PIN HEADER - THE OSTTH IS THE PLUG-ON SCREW TERMINAL
Revision B: Added R36,R45,C7. Unconnected Arduino VIN to +12V. Fixed PCB routing issue. Moved TOOL4_DOUT_BUF and !TOOL4_EN_BUF! from 18/19 to
TODO: INSTALL FERRITE BEAD ON ISENSE?
Change to SMD pads, bottom
Remove?
Replace

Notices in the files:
EAGLE/EMC03 - Motion Control/EMC02-Chopped.brd:
CC-BY-SA 4.0 license
EAGLE/EMC03 - Motion Control/EMC03-BOMEAGLE.csv:
LOGO-CC-BY-SALARGE;LOGO-CC-BY-SALARGE;LOGO-CC-BY-SA;;EXCLUDE;T;
parts and their libraries:
SparkFun-Capacitors: Licensing: Creative Commons ShareAlike 4.0 International - https://creativecommons.org/licenses/by-sa/4.0
SparkFun-Resistors: Licensing: CC v3.0 Share-Alike You are welcome to use this library for commercial purposes.
